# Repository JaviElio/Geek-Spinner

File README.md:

# Geek-Spinner
POV Spinner

Based on this project: 
	
	- Title:	GEEK SPINNER	
	- Author:	MakersBox
	- Link:		http://www.instructables.com/id/Geek-Spinner/

**BOM**

	- Attiny84-20SSU
	- 8 x 3 mm Red leds
	- SMD Blue led
	- 8 x 330mOhms resistors
	- Push button
	- CR2032 battery holder: 	https://lcsc.com/product-detail/Battery-Holders-Clips-Contacts_CR2032Curved-feet-3V_C70373.html
	- 2 x 0.1uF capacitors
	- TLE4906 Hall sensor: 		https://lcsc.com/product-detail/Sensors_Infineon_TLE4906KHTSA1_TLE4906KHTSA1_C126652.html
	- SMD switch : 			https://lcsc.com/product-detail/Toggle-Switches_9mm-3-5mm_C92658.html
	- 2x3 header: 			https://lcsc.com/product-detail/Male-Header_Headers-Pins-2-3P-2-54mm-SMD_C124390.html
	- 608 bearing: 			https://www.aliexpress.com/item/New-High-Speed-608-Hybrid-Ceramic-Center-Bearing-For-Fidget-Hand-spinner-ToyBBC/32817310812.html?spm=a2g0s.9042311.0.0.Zu7Bp7
	- 2x1mm neodynium magnet:	https://www.aliexpress.com/item/Free-shipping-10PCS-magnets-2mmx1mm-Tiny-Disc-Neodymium-Rare-Earth-Magnet-2x1-Craft-Model-2-1/32719568312.html?spm=a2g0s.9042311.0.0.u8fnqV

**3D Model**

**Video**

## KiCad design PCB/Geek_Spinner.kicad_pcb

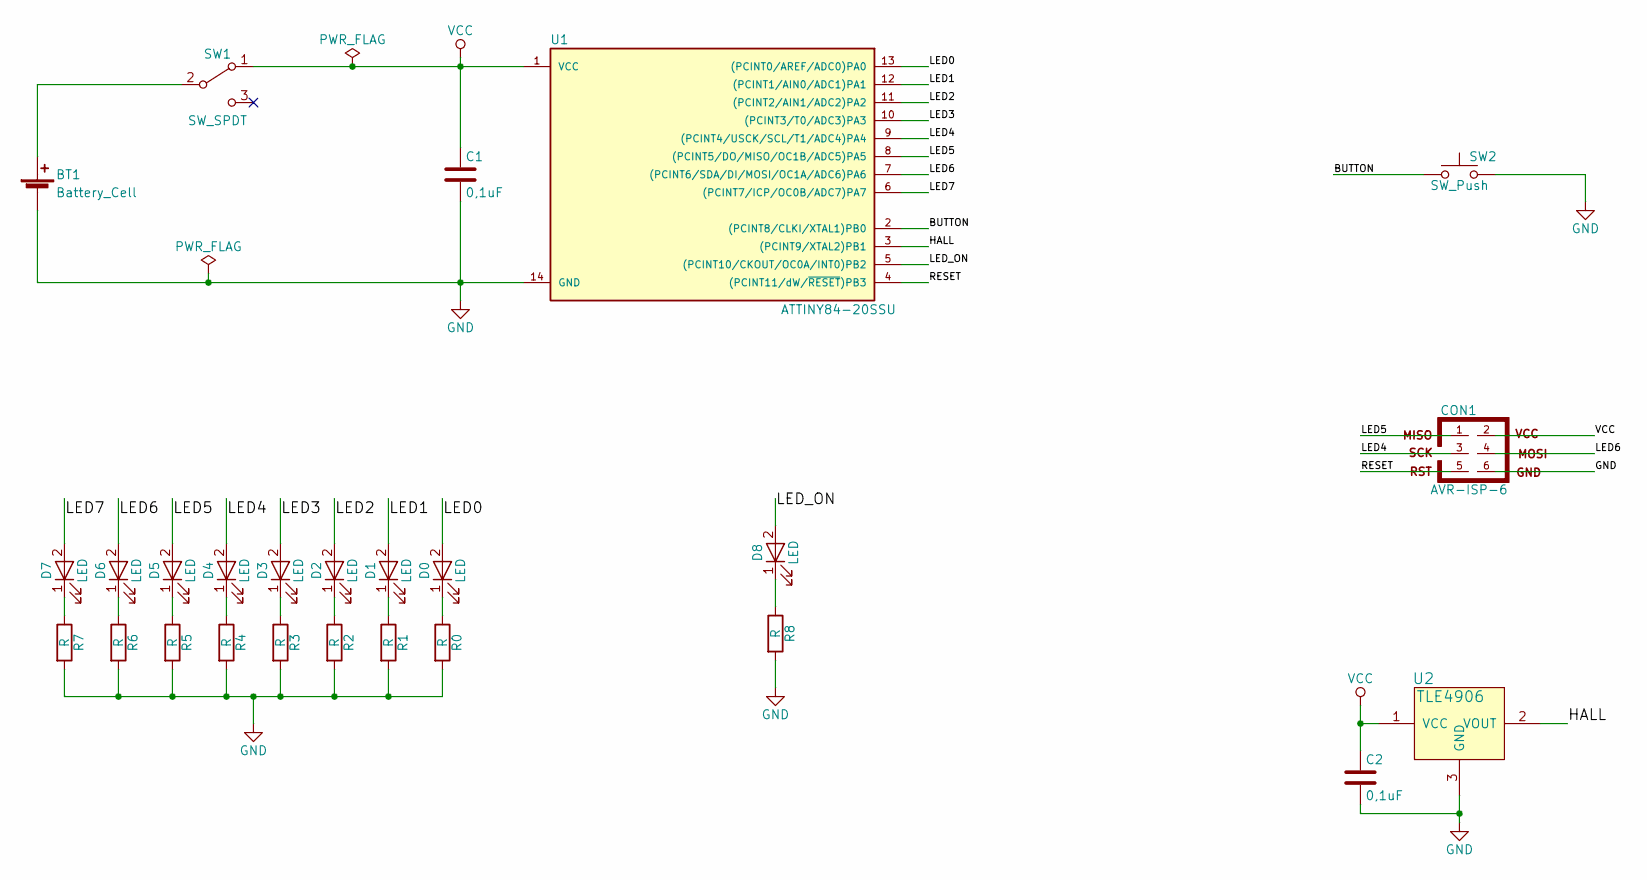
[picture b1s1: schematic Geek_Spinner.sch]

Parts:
BT1: Battery_Cell; CR2032_Holder_THT
C1, C2: 0,1uF; C_0805_HandSoldering
CON1: AVR-ISP-6; Pin_Header_Straight_2x03_Pitch2.54mm_SMD
D0, D1, D2, D3, D4, D5, D6, D7: LED; LED_D3.0mm
D8: LED; LED_0805_HandSoldering
R0, R1, R2, R3, R4, R5, R6, R7, R8: R; R_0805_HandSoldering
SW1: SW_SPDT; SW_SPDT_CK-JS102011SAQN
SW2: SW_Push; SW_PUSH_6mm_h4.3mm
U1: ATTINY84-20SSU; SOIC-14_3.9x8.7mm_Pitch1.27mm
U2: TLE4906; SC-59_Handsoldering

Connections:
/BUTTON: SW2.1, U1.2 ((PCINT8/CLKI/XTAL1)PB0)
/HALL: U1.3 ((PCINT9/XTAL2)PB1), U2.2 (VOUT)
/LED0: D0.2 (A), U1.13 ((PCINT0/AREF/ADC0)PA0)
/LED1: D1.2 (A), U1.12 ((PCINT1/AIN0/ADC1)PA1)
/LED2: D2.2 (A), U1.11 ((PCINT2/AIN1/ADC2)PA2)
/LED3: D3.2 (A), U1.10 ((PCINT3/T0/ADC3)PA3)
/LED4: CON1.3, D4.2 (A), U1.9 ((PCINT4/USCK/SCL/T1/ADC4)PA4)
/LED5: CON1.1, D5.2 (A), U1.8 ((PCINT5/DO/MISO/OC1B/ADC5)PA5)
/LED6: CON1.4, D6.2 (A), U1.7 ((PCINT6/SDA/DI/MOSI/OC1A/ADC6)PA6)
/LED7: D7.2 (A), U1.6 ((PCINT7/ICP/OC0B/ADC7)PA7)
/LED_ON: D8.2 (A), U1.5 ((PCINT10/CKOUT/OC0A/INT0)PB2)
/RESET: CON1.5, U1.4 ((PCINT11/dW/~RESET~)PB3)
GND: BT1.2 (-), C1.2, C2.2, CON1.6, R0.2, R1.2, R2.2, R3.2, R4.2, R5.2, R6.2, R7.2, R8.2, SW2.2, U1.14 (GND), U2.3 (GND)
unnamed: BT1.1 (+), SW1.2 (B)
unnamed: D0.1 (K), R0.1
unnamed: D1.1 (K), R1.1
unnamed: D2.1 (K), R2.1
unnamed: D3.1 (K), R3.1
unnamed: D4.1 (K), R4.1
unnamed: D5.1 (K), R5.1
unnamed: D6.1 (K), R6.1
unnamed: D7.1 (K), R7.1
unnamed: D8.1 (K), R8.1
VCC: C1.1, C2.1, CON1.2, SW1.1 (A), U1.1 (VCC), U2.1 (VCC)

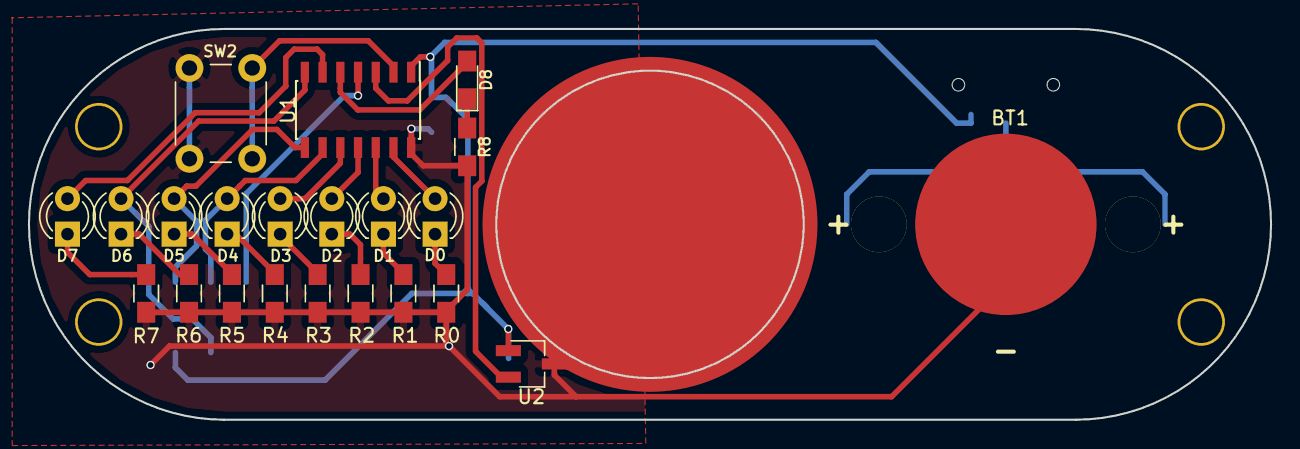
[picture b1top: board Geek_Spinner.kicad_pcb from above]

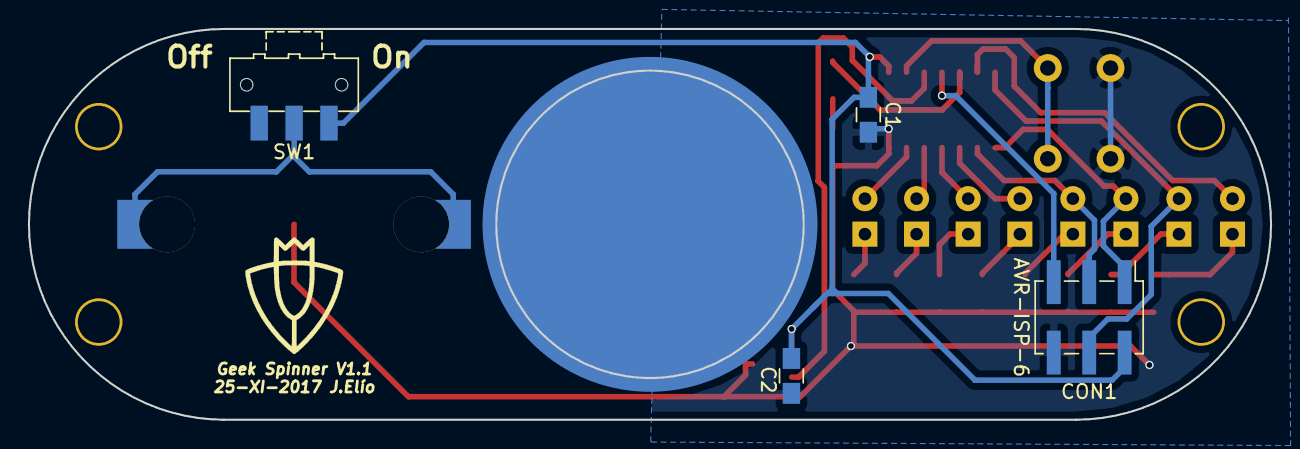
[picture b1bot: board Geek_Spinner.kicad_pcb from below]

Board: 2 copper layers, 89.0 x 28.0 mm, 26 parts (4 on the bottom side), 24 nets.

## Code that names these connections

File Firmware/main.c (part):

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

uint8_t spinning = 0;							// spinning -> 1 / not spinning -> 0
volatile uint8_t magnetFlag = 0;				// hall sensor activation flag
uint8_t mode = 1;								// Led mode

volatile uint16_t revs = 0;						// total revolutions
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	
	while (!(PINB & (1 << PINB0))) {			// Wait until button is released
		PORTA = (1 << (mode -1));				// Show active mode while button is pressed
		PORTB &= ~(1 << PB2);					// Blue led off
		_delay_ms(50);
	}

	PORTA = 0x00;								// Switch off leds
	PORTB |= (1 << PB2);						// Blue led off
}

// Returns delay in us
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
	// Set I/O
	DDRA	=	0xFF;					// PORTA outputs (red leds)
	DDRB	|=	(1 << PB2);				// PB2 output (blue led)
 	DDRB	&=	~(1 << DDB0);			// PB0 input (Button)
 	DDRB	&=  ~(1 << DDB1);			// PB1 input (Hall Sensor)
	PORTB	|=	(1 << PB0);				// Pull-Up resistor
	PORTB	|=	(1 << PB1);				// Pull-Up resistor	

	// Set Timer0
	TCCR0B	|=	(1 << CS01);			// Start timer0 and set prescaler clk/8
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	set_sleep_mode(SLEEP_MODE_PWR_DOWN);

	// Set interrupt
	PCMSK1	|=	(1 << PCINT9);			// Enable pin interrupt at PB1
	GIMSK	|=	(1 << PCIE1);			// Enable pin change interrupt 1
	sei();								// Enable global interrupts
	
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		if (oldTimer0_OV >= 800 || timer0_OV > 800)
		{
			spinning = 0;
			PORTB |= (1 << PB2);						// Blue led on
		}
		 else if (oldTimer0_OV < 800)
		 {
			 spinning = 1;
			 PORTB &= ~(1 << PB2);						// Blue led off
		 }
	
	
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		 // If spinner is stopped during 16s. (aprox) then sleep
		 if (timer0_OV >= 65500) {
			
			PORTB &= ~(1 << PB2);									// Blue led off
			WDTCSR |= (1 << WDCE) | (1 << WDE);						// Enable WatchDog
			WDTCSR |= (1 << WDIE) | (1 << WDP3);					// Set prescaler to 4s

			sleep_mode();								// go to sleep

			PORTB |= (1 << PB2);						// Blue led on
			_delay_ms(15);
			PORTB &= ~(1 << PB2);						// Blue led off	

		 }
				
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
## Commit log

2018-03-05 First upload
2018-03-10 Added more modes
2018-03-11 Deep Sleep mode added
2018-03-11 indentation added
2018-03-12 Readme updated
2018-03-12 picture added
2018-03-12 Picture changed
2018-03-14 Polish details
2018-03-26 Readmed updated
